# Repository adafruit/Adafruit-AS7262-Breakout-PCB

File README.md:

## Adafruit AS7262 Channel Visible Light / Color Sensor Breakout PCB

<a href="http://www.adafruit.com/products/3779"><br/>
Click here to purchase one from the Adafruit shop</a>

PCB files for AS7262 breakout. Format is EagleCAD schematic and board layout

For more details, check out the product page at
* https://www.adafruit.com/products/3779

### Description

Detect trees of green, and red roses too with the new Adafruit AS7262 6-Channel Visible Light / Color Sensor Breakout. This sensor from AMS has 6 integrated visible light sensing channels for red, orange, yellow, green, blue, and violet. These channels can be read via the I2C bus as either raw 16-bit values or calibrated floating-point values. There is also an on-board temperature sensor that can be used to read the temperature of the chip, and a powerful LED flash to reflect light off objects for better color detection.

The 6 channels on the AS7262 are realized by silicon interference filters at 450nm, 500nm, 550nm, 570nm, 600nm, and 650nm. This breakout uses the I2C interface on the chip by default, but a UART interface that accepts AT commands is also selectable.

We've placed the sensor on a PCB for you and included an SPI flash chip pre-programmed with the device firmware, a 3.3V regulator, I2C level shifting, and the recommended LED flash. Both the I2C and UART interfaces are broken out, making this breakout an excellent all-in-one solution for all your color-sensing needs. The pinout for the UART interface is plug-and-play compatible with the Adafruit FTDI Friend.

### License

Adafruit invests time and resources providing this open source design, please support Adafruit and open-source hardware by purchasing products from [Adafruit](https://www.adafruit.com)!

Designed by Limor Fried/Ladyada for Adafruit Industries.

Creative Commons Attribution/Share-Alike, all text above must be included in any redistribution. See license.txt for additional details.

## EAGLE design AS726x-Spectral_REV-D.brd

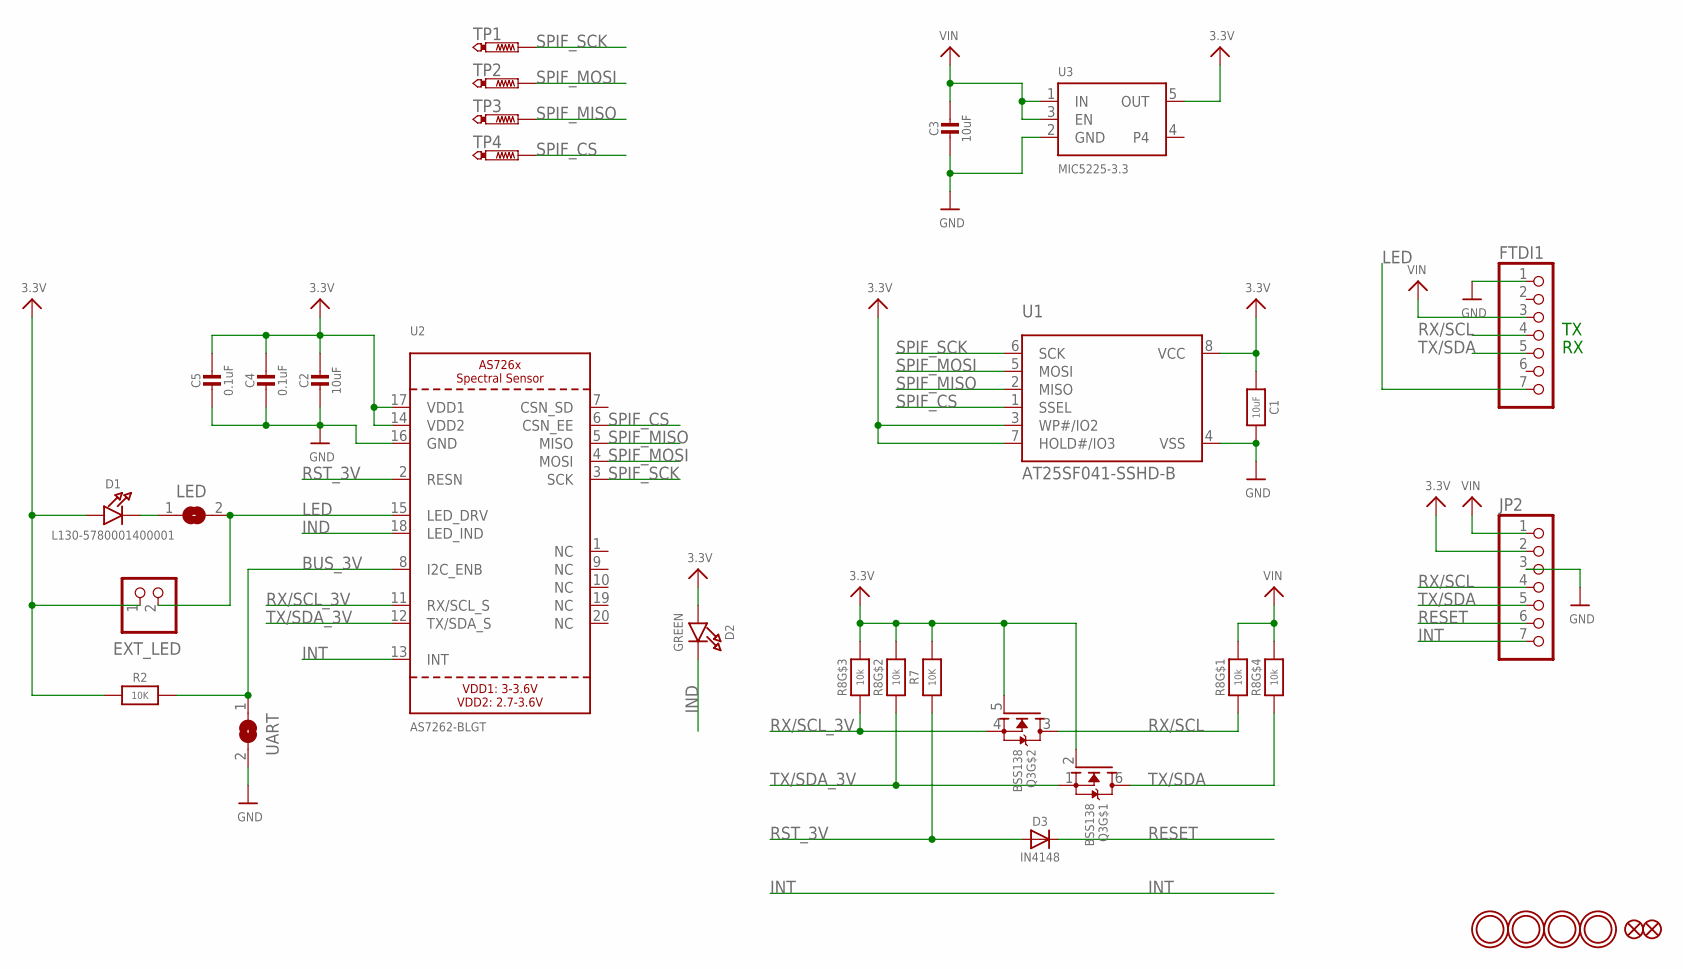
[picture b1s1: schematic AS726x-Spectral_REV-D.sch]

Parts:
C1, C2, C3: 10uF; 0805-NO
C4, C5: 0.1uF; 0603-NO
D1: L130-5780001400001; EVERLIGHT_45-21
D2: GREEN; CHIPLED_0805_NOOUTLINE
D3: IN4148; SOD-323
EXT_LED: HEADER-1X2ROUND; 1X02_ROUND
FID2, FID3: FIDUCIAL_1MM
FTDI1: HEADER-1X7ROUND; 1X07_ROUND
JP2: HEADER-1X7ROUND; 1X07_ROUND
LED: SOLDERJUMPERCLOSED; SOLDERJUMPER_CLOSEDWIRE
Q3: BSS138; SOT363
R2: 10K; 0805-NO
R7: 10K; 0603-NO
R8: 10k; RESPACK_4X0603_NO
TP1, TP2, TP3, TP4: PTR1TP15R; TP15R
U1: AT25SF041-SSHD-B; SOIC8_150MIL
U2: AS7262-BLGT; AS726X_LGA20
U3: MIC5225-3.3; SOT23-5
U$2, U$3, U$22, U$23: MOUNTINGHOLE2.5; MOUNTINGHOLE_2.5_PLATED
UART: SOLDERJUMPER; SOLDERJUMPER_ARROW_NOPASTE

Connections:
3.3V: C1.1, C2.1, C4.1, C5.1, D1.A, D2.A, EXT_LED.1, JP2.2, Q3.2 (G), Q3.5 (G), R2.1, R7.2, R8.6 (2), R8.7 (2), U1.3 (WP#/IO2), U1.7 (HOLD#/IO3), U1.8 (VCC), U2.14 (VDD2), U2.17 (VDD1), U3.5 (OUT)
BUS_3V: R2.2, U2.8 (I2C_ENB), UART.1
GND: C1.2, C2.2, C3.2, C4.2, C5.2, FTDI1.1, JP2.3, U1.4 (VSS), U2.16 (GND), U3.2 (GND), UART.2
IND: D2.C, U2.18 (LED_IND)
INT: JP2.7, U2.13 (INT)
LED: EXT_LED.2, FTDI1.7, LED.2, U2.15 (LED_DRV)
unnamed: D1.K (C), LED.1
RESET: D3.C, JP2.6
RST_3V: D3.A, R7.1, U2.2 (RESN)
RX/SCL: FTDI1.4, JP2.4, Q3.3 (D), R8.1
RX/SCL_3V: Q3.4 (S), R8.3 (1), U2.11 (RX/SCL_S)
SPIF_CS: TP4.TP, U1.1 (SSEL), U2.6 (CSN_EE)
SPIF_MISO: TP3.TP, U1.2 (MISO), U2.5 (MISO)
SPIF_MOSI: TP2.TP, U1.5 (MOSI), U2.4 (MOSI)
SPIF_SCK: TP1.TP, U1.6 (SCK), U2.3 (SCK)
TX/SDA: FTDI1.5, JP2.5, Q3.6 (D), R8.4 (1)
TX/SDA_3V: Q3.1 (S), R8.2 (1), U2.12 (TX/SDA_S)
VIN: C3.1, FTDI1.3, JP2.1, R8.5 (2), R8.8 (2), U3.1 (IN), U3.3 (EN)

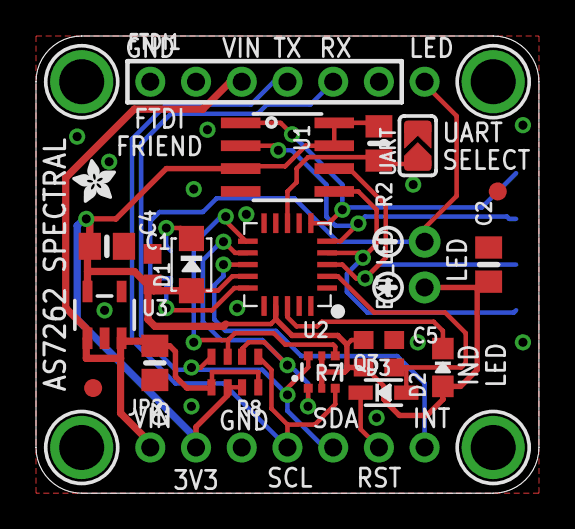
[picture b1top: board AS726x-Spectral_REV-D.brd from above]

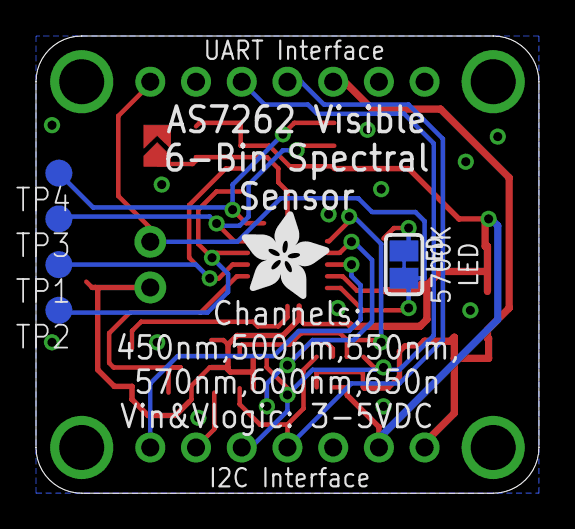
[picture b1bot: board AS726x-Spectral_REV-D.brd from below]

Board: 2 copper layers, 27.9 x 25.4 mm, 34 parts (6 on the bottom side), 18 nets.

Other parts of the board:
U$9: ADAFRUIT_5MM
U$21: ADAFRUIT_2.5MM
U$25: SYMBOL_PLUS
U$26: SYMBOL_MINUS

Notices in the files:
parts and their libraries:
microbuilder: This work is placed in the public domain, and may be freely used for commercial and non-commercial work with the following conditions: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
